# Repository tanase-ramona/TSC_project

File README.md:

## EBookReader

Am început realizarea proiectului pornind de la schema electrică oferită în enunț. Am adăugat fiecare componentă din biblioteca sugerata și le-am conectat corespunzător, atribuindu-le etichete adecvate. După finalizarea conexiunilor, am rulat o verificare ERC pentru a identifica eventualele erori si am rezolvat marea majoritate. A rămas o singură eroare nerezolvată, deoarece Fusion nu a putut indica locația acesteia. După ce schema a fost finalizată, am trecut la partea de PCB. Am decupat placa conform dimensiunilor cerute folosind masuratorile oferite de Fusion. Cea mai mare provocare a fost identificarea și poziționarea corectă a componentelor pe PGB. După plasare, am realizat rutarea și am validat designul în funcție de regulile specificate în enunț. Pentru a elimina erorile, a fost necesară modificarea footprint-ului pentru anumite piese. În final, am realizat planul de masă atât pentru stratul superior, cât și pentru cel inferior.

## Arhitectură Generală a Sistemului

## Descriere Generală

Modulul **ESP32-C6-WROOM-1-N8** este nucleul sistemului, facilitând comunicarea cu toate celelalte periferice prin interfețe standard precum I2C, SPI și GPIO. Alimentarea este realizată printr-o baterie Li-Po, gestionată de un controler de încărcare dedicat și monitorizată constant cu ajutorul unui fuel gauge.

## Componente Hardware

###  ESP32-C6
- Microcontroller cu procesor RISC-V
- Conectivitate Wi-Fi 6 și Bluetooth LE
- Interfețe: SPI, I2C, UART, GPIO
- Tensiune de operare: 3.3V

### Componente și resurse

| Componentă  | Link Achiziție | Datasheet |
|-------------|----------------|-----------|
| BOOT_BUTTON | https://ro.mouser.com/ProductDetail/Panasonic/EVQ-P7L01P | https://componentsearchengine.com/Datasheets/2/EVQP7L01P.pdf |
| C1          | https://ro.mouser.com/ProductDetail/YAGEO/CC0402MRX5R5BB106 | https://componentsearchengine.com/Datasheets/2/CC0402MRX5R5BB106.pdf |
| C1_BAT      | https://ro.mouser.com/ProductDetail/YAGEO/CC0402MRX5R5BB106 | https://componentsearchengine.com/Datasheets/2/CC0402MRX5R5BB106.pdf |
| C2          | https://ro.mouser.com/ProductDetail/YAGEO/CC0402MRX5R5BB106 | https://componentsearchengine.com/Datasheets/2/CC0402MRX5R5BB106.pdf |
| C2_BAT      | https://ro.mouser.com/ProductDetail/YAGEO/CC0402MRX5R5BB106 | https://componentsearchengine.com/Datasheets/2/CC0402MRX5R5BB106.pdf |
| C3          | https://ro.mouser.com/ProductDetail/YAGEO/CC0402MRX5R5BB106 | https://componentsearchengine.com/Datasheets/2/CC0402MRX5R5BB106.pdf |
| C4          | https://ro.mouser.com/ProductDetail/YAGEO/CC0402MRX5R5BB106 | https://componentsearchengine.com/Datasheets/2/CC0402MRX5R5BB106.pdf |
| C4_USB      | https://ro.mouser.com/ProductDetail/YAGEO/CC0402MRX5R5BB106 | https://componentsearchengine.com/Datasheets/2/CC0402MRX5R5BB106.pdf |
| C5          | https://ro.mouser.com/ProductDetail/YAGEO/CC0402MRX5R5BB106 | https://componentsearchengine.com/Datasheets/2/CC0402MRX5R5BB106.pdf |
| C5_USB      | https://ro.mouser.com/ProductDetail/YAGEO/CC0402MRX5R5BB106 | https://componentsearchengine.com/Datasheets/2/CC0402MRX5R5BB106.pdf |
| C6          | https://ro.mouser.com/ProductDetail/YAGEO/CC0402MRX5R5BB106 | https://componentsearchengine.com/Datasheets/2/CC0402MRX5R5BB106.pdf |
| C7          | https://ro.mouser.com/ProductDetail/YAGEO/CC0402MRX5R5BB106 | https://componentsearchengine.com/Datasheets/2/CC0402MRX5R5BB106.pdf |
| C8          | https://ro.mouser.com/ProductDetail/YAGEO/CC0402MRX5R5BB106 | https://componentsearchengine.com/Datasheets/2/CC0402MRX5R5BB106.pdf |
| C9          | https://ro.mouser.com/ProductDetail/YAGEO/CC0402MRX5R5BB106 | https://componentsearchengine.com/Datasheets/2/CC0402MRX5R5BB106.pdf |
| C10         | https://ro.mouser.com/ProductDetail/YAGEO/CC0402MRX5R5BB106 | https://componentsearchengine.com/Datasheets/2/CC0402MRX5R5BB106.pdf |
| D1          | https://ro.mouser.com/ProductDetail/STMicroelectronics/STPS2L30A | https://www.st.com/resource/en/datasheet/stps2l30.pdf |
| D2          | https://ro.mouser.com/ProductDetail/STMicroelectronics/STPS2L30A | https://www.st.com/resource/en/datasheet/stps2l30.pdf |
| D3          | https://ro.mouser.com/ProductDetail/STMicroelectronics/STPS2L30A | https://www.st.com/resource/en/datasheet/stps2l30.pdf |
| D4          | https://ro.mouser.com/ProductDetail/STMicroelectronics/STPS2L30A | https://www.st.com/resource/en/datasheet/stps2l30.pdf |
| IC1         | https://ro.mouser.com/ProductDetail/Texas-Instruments/BQ24075RGTT | https://www.ti.com/lit/ds/symlink/bq24075.pdf |
| Q1          | https://ro.mouser.com/ProductDetail/Diodes-Incorporated/DMG2305UX-7 | https://www.diodes.com/assets/Datasheets/ds31771.pdf |
| Q2          | https://ro.mouser.com/ProductDetail/Diodes-Incorporated/DMG2305UX-7 | https://www.diodes.com/assets/Datasheets/ds31771.pdf |
| Q3          | https://ro.mouser.com/ProductDetail/Diodes-Incorporated/DMG2305UX-7 | https://www.diodes.com/assets/Datasheets/ds31771.pdf |
| Q4          | https://ro.mouser.com/ProductDetail/Diodes-Incorporated/DMG2305UX-7 | https://www.diodes.com/assets/Datasheets/ds31771.pdf |
| R1          | https://ro.mouser.com/ProductDetail/YAGEO/RC0402FR-0710KL | https://componentsearchengine.com/Datasheets/2/RC0402FR-0710KL.pdf |
| R2          | https://ro.mouser.com/ProductDetail/YAGEO/RC0402FR-0710KL | https://componentsearchengine.com/Datasheets/2/RC0402FR-0710KL.pdf |
| R3          | https://ro.mouser.com/ProductDetail/YAGEO/RC0402FR-0710KL | https://componentsearchengine.com/Datasheets/2/RC0402FR-0710KL.pdf |
| R4          | https://ro.mouser.com/ProductDetail/YAGEO/RC0402FR-0710KL | https://componentsearchengine.com/Datasheets/2/RC0402FR-0710KL.pdf |
| R5           | https://ro.mouser.com/ProductDetail/YAGEO/RC0402FR-07100KL | https://ro.mouser.com/datasheet/2/447/YAGEO_PYu_RC_Group_51_RoHS_L_12-3313492.pdf |
| R6           | https://ro.mouser.com/ProductDetail/YAGEO/RC0402FR-07100KL | https://ro.mouser.com/datasheet/2/447/YAGEO_PYu_RC_Group_51_RoHS_L_12-3313492.pdf |
| R7           | https://ro.mouser.com/ProductDetail/YAGEO/RC0402FR-07100KL | https://ro.mouser.com/datasheet/2/447/YAGEO_PYu_RC_Group_51_RoHS_L_12-3313492.pdf |
| R8           | https://ro.mouser.com/ProductDetail/YAGEO/RC0402FR-07100KL | https://ro.mouser.com/datasheet/2/447/YAGEO_PYu_RC_Group_51_RoHS_L_12-3313492.pdf |
| R9           | https://ro.mouser.com/ProductDetail/YAGEO/RC0402FR-07100KL | https://ro.mouser.com/datasheet/2/447/YAGEO_PYu_RC_Group_51_RoHS_L_12-3313492.pdf |
| R10          | https://ro.mouser.com/ProductDetail/YAGEO/RC0402FR-07100KL | https://ro.mouser.com/datasheet/2/447/YAGEO_PYu_RC_Group_51_RoHS_L_12-3313492.pdf |
| RESET_BUTTON | https://ro.mouser.com/ProductDetail/Panasonic/EVQ-P7L01P | https://componentsearchengine.com/Datasheets/2/EVQP7L01P.pdf |
| R_BOOT       | https://ro.mouser.com/ProductDetail/YAGEO/RC0402FR-07100KL | https://ro.mouser.com/datasheet/2/447/YAGEO_PYu_RC_Group_51_RoHS_L_12-3313492.pdf |
| R_CAPACITOR  | https://ro.mouser.com/ProductDetail/YAGEO/RC0402FR-07100KL | https://ro.mouser.com/datasheet/2/447/YAGEO_PYu_RC_Group_51_RoHS_L_12-3313492.pdf |
| R_CHANGE     | https://ro.mouser.com/ProductDetail/YAGEO/RC0402FR-07100KL | https://ro.mouser.com/datasheet/2/447/YAGEO_PYu_RC_Group_51_RoHS_L_12-3313492.pdf |
| R_CL1        | https://ro.mouser.com/ProductDetail/YAGEO/RC0402FR-07100KL | https://ro.mouser.com/datasheet/2/447/YAGEO_PYu_RC_Group_51_RoHS_L_12-3313492.pdf |
| R_RESET      | https://ro.mouser.com/ProductDetail/YAGEO/RC0402FR-07100KL | https://ro.mouser.com/datasheet/2/447/YAGEO_PYu_RC_Group_51_RoHS_L_12-3313492.pdf |
| SENSOR2      | https://ro.mouser.com/ProductDetail/Bosch-Sensortec/BME680 | https://ro.mouser.com/datasheet/2/783/BST_BME680_DS001-1509608.pdf |
| SJ1          | https://grabcad.com/library/solder-jumpers-1 | https://grabcad.com/library/solder-jumpers-1 |
| U1           | https://ro.mouser.com/ProductDetail/Winbond/W25Q512JVEIQ | https://ro.mouser.com/datasheet/2/949/Winbond_W25Q512JV_Datasheet-3240039.pdf |
| U2           | https://ro.mouser.com/ProductDetail/Espressif-Systems/ESP32-C6-WROOM-1-N8 | https://ro.mouser.com/datasheet/2/891/Espressif_ESP32_C6_WROOM_1__Datasheet_V0_1_PRELIMI-3239987.pdf |
| U3           | https://ro.mouser.com/ProductDetail/Analog-Devices-Maxim-Integrated/DS3231SN | https://ro.mouser.com/datasheet/2/609/DS3231-3421123.pdf |
| U4           | https://ro.mouser.com/ProductDetail/Analog-Devices-Maxim-Integrated/MAX17048G+T10 | https://ro.mouser.com/datasheet/2/609/MAX17048_MAX17049-3469099.pdf |
| U5           | https://ro.mouser.com/ProductDetail/Microchip-Technology/MCP73831T-2ACI-OT | https://ro.mouser.com/datasheet/2/268/MCP73831_Family_Data_Sheet_DS20001984H-3441711.pdf |

###  Sistem de Alimentare
- **MCP73831** – controler de încărcare pentru baterii LiPo
- **MAX17048** – fuel gauge pentru măsurarea nivelului de baterie și avertizare
- **XC6220A331MR** – stabilizator de tensiune 3.3V LDO

###  Protecție și Conectivitate
- Protecție ESD pentru liniile USB (USBLC6)
- Diode Schottky pentru protecție la supratensiune
- Conector USB-C pentru alimentare și comunicație serială

###  Interfață Utilizator
- Buton RESET pentru restart manual
- LED pentru indicarea stării de încărcare

## Estimare Totală Consum în Funcționare Activă:
**~120 – 200 mA** (fără SD Card)

## Estimare Totală în Modul Sleep:
**< 100 µA** (cu ESP32 în deep sleep și periferice oprite)

---

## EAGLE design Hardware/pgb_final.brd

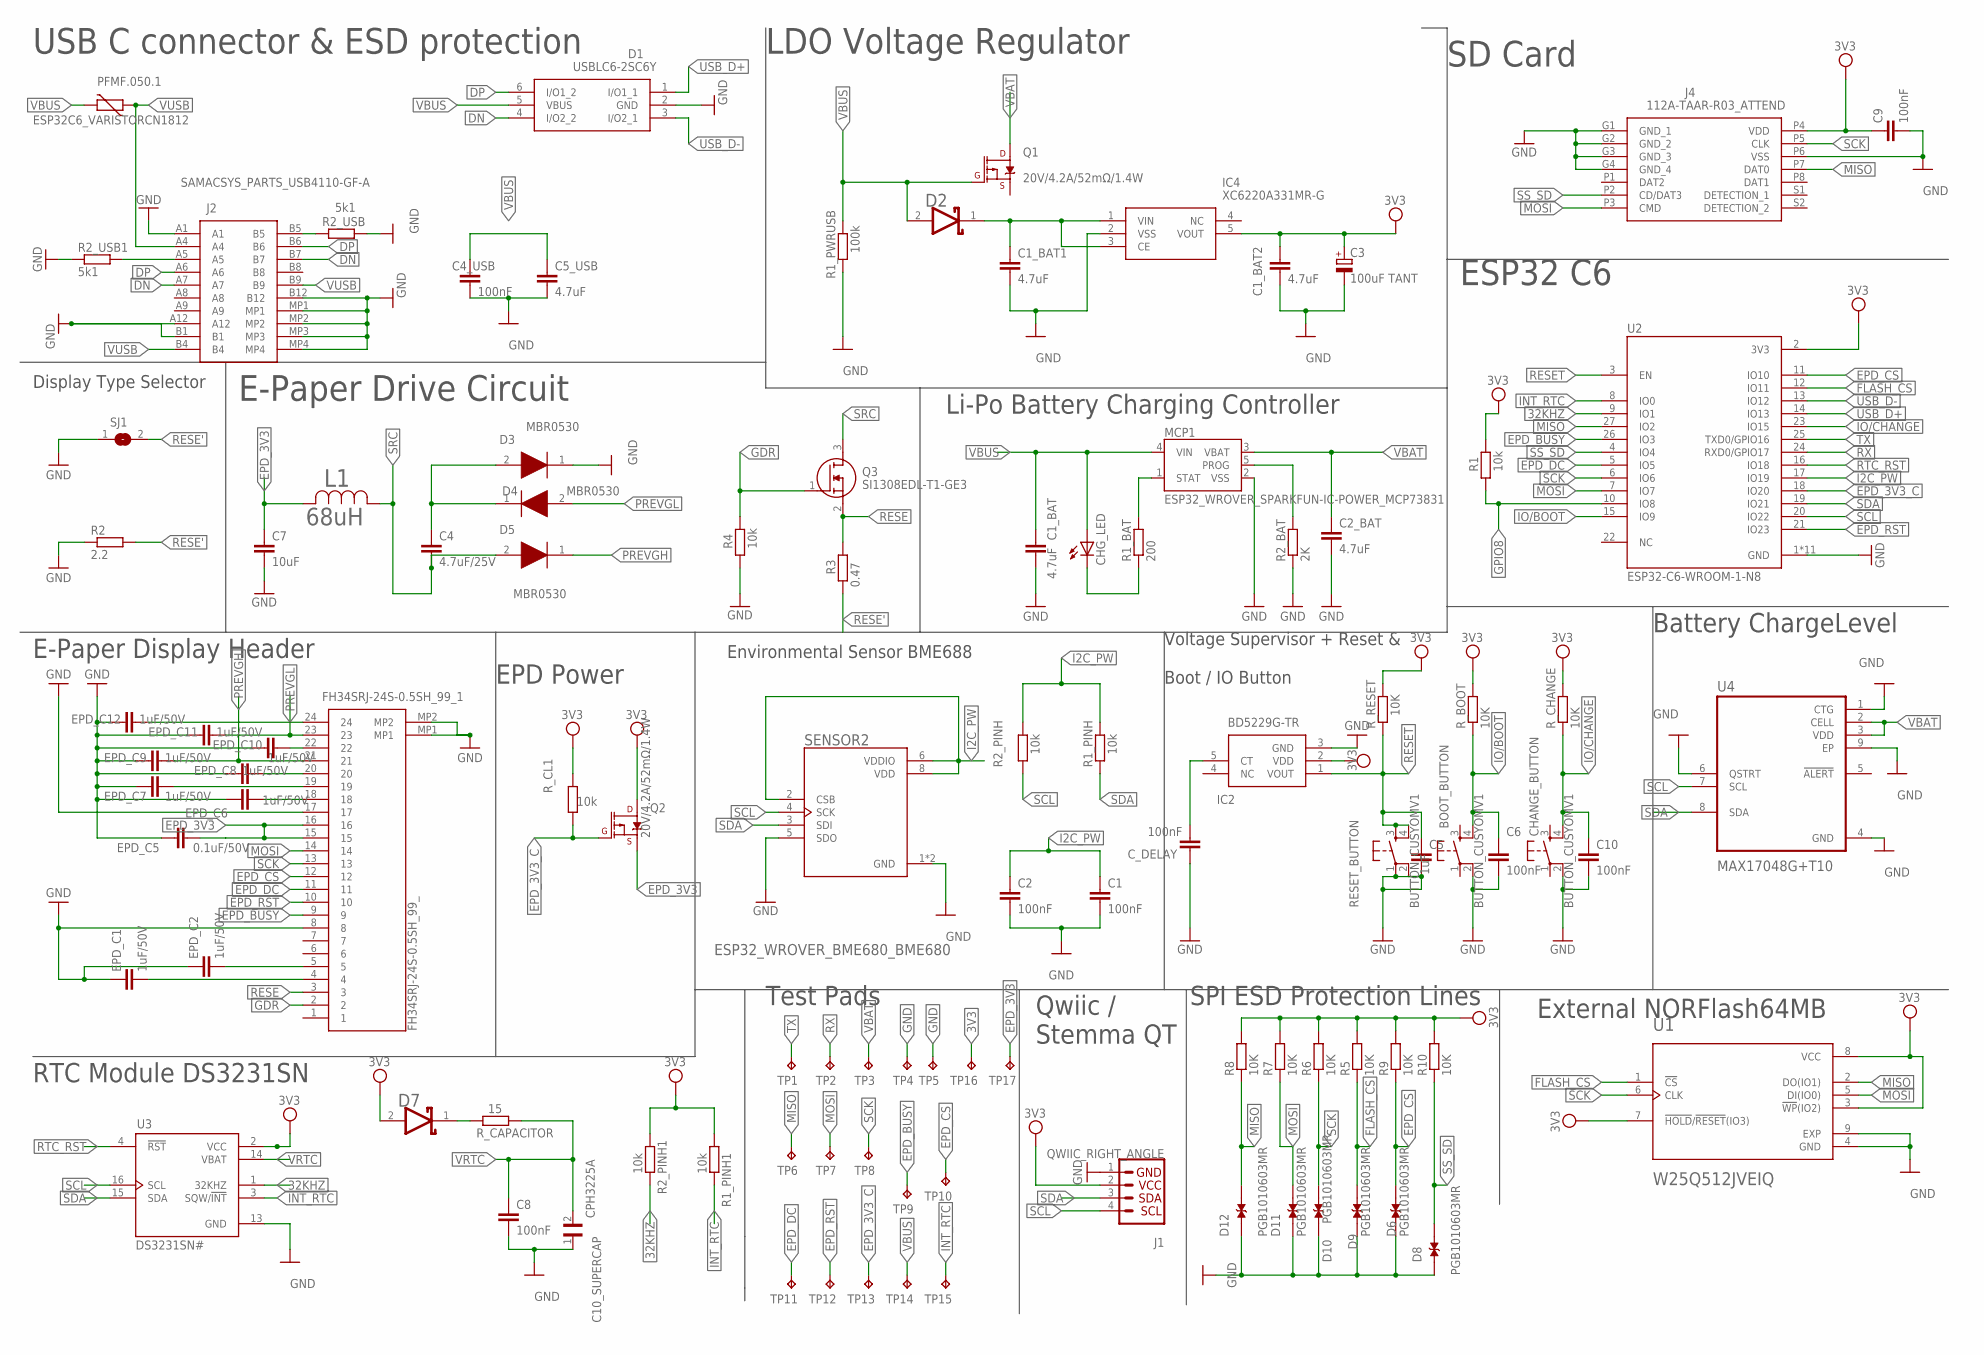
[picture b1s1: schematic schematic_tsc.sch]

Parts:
BOOT_BUTTON: BUTTON_CUSYOMV1; MYBUTTON
C1, C2, C4_USB, C6, C8, C9, C10: 100nF; EAGLE-LTSPICE_C0402
C1_BAT, C1_BAT1, C1_BAT2, C2_BAT, C5_USB: 4.7uF; EAGLE-LTSPICE_C0402
C3: 100uF TANT; RCL_CT3528
C4: 4.7uF/25V; EAGLE-LTSPICE_C0402
C5: 1uF; EAGLE-LTSPICE_C0402
C7: 10uF; EAGLE-LTSPICE_C0402
C10_SUPERCAP: CPH3225A; CAPCP3225X100N
CHANGE_BUTTON: BUTTON_CUSYOMV1; MYBUTTON
CHG_LED: ADAFRUIT_LEDCHIP-LED0603; ADAFRUIT_CHIP-LED0603
C_DELAY: 100nF; EAGLE-LTSPICE_C0402
D1: USBLC6-2SC6Y; SOT95P280X145-6N
D2, D7: ESP32_WROVER_AVX---SD0805S020S1R0_AVX_SD0805S020S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; ESP32_WROVER_AVX---SD0805S020S1R0_AVX_SD0805S020S1R0_0
D3, D4, D5: MBR0530; SOD3716X135N
D6, D8, D9, D10, D11, D12: PGB1010603MR; DIOC1608X36N
EPD_C1, EPD_C2, EPD_C6, EPD_C7, EPD_C8, EPD_C9, EPD_C10, EPD_C11, EPD_C12: 1uF/50V; EAGLE-LTSPICE_C0402
EPD_C5: 0.1uF/50V; EAGLE-LTSPICE_C0402
FH34SRJ-24S-0.5SH_99_1: FH34SRJ-24S-0.5SH_99_; FH34SRJ24S05SH99
IC2: BD5229G-TR; SOT95P280X125-5N
IC4: XC6220A331MR-G; SOT95P280X120-5N
J1: QWIIC_RIGHT_ANGLE; JST04_1MM_RA
J2: SAMACSYS_PARTS_USB4110-GF-A; SAMACSYS_PARTS_USB4110GFA
J4: 112A-TAAR-R03_ATTEND; 112ATAARR03ATTEND
L1: 68uH; IND_4828-WE-TPC_WRE
MCP1: ESP32_WROVER_SPARKFUN-IC-POWER_MCP73831; ESP32_WROVER_SPARKFUN-IC-POWER_SOT23-5
PFMF.050.1: ESP32C6_VARISTORCN1812; ESP32C6_VARISTOR_CT/CN1812
Q1, Q2: 20V/4.2A/52mΩ/1.4W; ESP32_WROVER_SPARKFUN-DISCRETESEMI_SOT23-3
Q3: SI1308EDL-T1-GE3; SOT65P210X110-3N
R1, R1_PINH, R1_PINH1, R2_PINH, R2_PINH1, R4: 10k; ESP32_WROVER_EAGLE-LTSPICE_R0402
R1_BAT: 200; ESP32_WROVER_EAGLE-LTSPICE_R0402
R1_PWRUSB: 100k; ESP32_WROVER_EAGLE-LTSPICE_R0402
R2: 2.2; ESP32_WROVER_EAGLE-LTSPICE_R0402
R2_BAT: 2K; ESP32_WROVER_EAGLE-LTSPICE_R0402
R2_USB, R2_USB1: 5k1; ESP32_WROVER_EAGLE-LTSPICE_R0402
R3: 0.47; ESP32_WROVER_EAGLE-LTSPICE_R0402
R5, R6, R7, R8, R9, R10: 10K; ESP32_WROVER_EAGLE-LTSPICE_R0402
RESET_BUTTON: BUTTON_CUSYOMV1; MYBUTTON
R_BOOT: 10K; ESP32_WROVER_EAGLE-LTSPICE_R0402
R_CAPACITOR: 15; ESP32_WROVER_EAGLE-LTSPICE_R0402
R_CHANGE: 10K; ESP32_WROVER_EAGLE-LTSPICE_R0402
R_CL1: 10k; ESP32_WROVER_EAGLE-LTSPICE_R0402
R_RESET: 10K; ESP32_WROVER_EAGLE-LTSPICE_R0402
SENSOR2: ESP32_WROVER_BME680_BME680; ESP32_WROVER_BME680_PSON80P300X300X100-8N
SJ1: SJ
TP1, TP2, TP3, TP4, TP5, TP6, TP7, TP8, TP9, TP10, TP11, TP12, TP13, TP14, TP15, TP16, TP17: TPTP20R; TP20R
U1: W25Q512JVEIQ; SON127P600X800X80-9N
U2: ESP32-C6-WROOM-1-N8; XCVR_ESP32-C6-WROOM-1-N8
U3: DS3231SN#; SOIC127P1032X265-16N
U4: MAX17048G+T10; SON50P200X200X80-9N

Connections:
3V3: C1_BAT2.1, C3.+, C9.1, D7.2 (ANODE), IC2.2 (VDD), IC4.5 (VOUT), J1.2, J4.P4 (VDD), Q2.3 (D), R1.2, R1_PINH1.1, R2_PINH1.1, R5.2, R6.2, R7.2, R8.2, R9.2, R10.2, R_BOOT.2, R_CHANGE.2, R_CL1.2, R_RESET.2, TP16.TP, U1.3 (!WP!(IO2)), U1.7 (!HOLD!/!RESET!(IO3)), U1.8 (VCC), U2.2 (3V3), U3.2 (VCC)
32KHZ: R2_PINH1.2, U2.9 (IO1), U3.1 (32KHZ)
DN: D1.4 (I/O2_2), J2.A7, J2.B7
DP: D1.6 (I/O1_2), J2.A6, J2.B6
EPD_3V3: C7.1, EPD_C5.2, FH34SRJ-24S-0.5SH_99_1.15, FH34SRJ-24S-0.5SH_99_1.16, L1.2, Q2.2 (S), TP17.TP
EPD_3V3_C: Q2.1 (G), R_CL1.1, TP13.TP, U2.18 (IO20)
EPD_BUSY: FH34SRJ-24S-0.5SH_99_1.9, TP9.TP, U2.26 (IO3)
EPD_CS: D6.2, FH34SRJ-24S-0.5SH_99_1.12, R9.1, TP10.TP, U2.11 (IO10)
EPD_DC: FH34SRJ-24S-0.5SH_99_1.11, TP11.TP, U2.5 (IO5)
EPD_RST: FH34SRJ-24S-0.5SH_99_1.10, TP12.TP, U2.21 (IO23)
FLASH_CS: D9.2, R5.1, U1.1 (!CS), U2.12 (IO11)
GDR: FH34SRJ-24S-0.5SH_99_1.2, Q3.1 (G), R4.2
GND: BOOT_BUTTON.2, C1.2, C1_BAT.2, C1_BAT1.2, C1_BAT2.2, C2.2, C2_BAT.2, C3.-, C4_USB.2, C5.2, C5_USB.2, C6.2, C7.2, C8.2, C9.2, C10.2, C10_SUPERCAP.1, CHANGE_BUTTON.2, C_DELAY.1, D1.2 (GND), D3.1 (K), D6.1, D8.1, D9.1, D10.1, D11.1, D12.1, EPD_C1.1, EPD_C2.1, EPD_C5.1, EPD_C6.1, EPD_C7.1, EPD_C8.1, EPD_C9.1, EPD_C10.1, EPD_C11.1, EPD_C12.1, FH34SRJ-24S-0.5SH_99_1.8, FH34SRJ-24S-0.5SH_99_1.17, FH34SRJ-24S-0.5SH_99_1.MP1, FH34SRJ-24S-0.5SH_99_1.MP2, IC2.3 (GND), IC4.2 (VSS), J1.1, J2.A1, J2.A12, J2.B1, J2.B12, J2.MP1, J2.MP2, J2.MP3, J2.MP4, J4.G1 (GND_1), J4.G2 (GND_2), J4.G3 (GND_3), J4.G4 (GND_4), J4.P6 (VSS), MCP1.2 (VSS), R1_PWRUSB.1, R2.1, R2_BAT.1, R2_USB.2, R2_USB1.1, R4.1, RESET_BUTTON.1, RESET_BUTTON.2, SENSOR2.1 (GND), SENSOR2.5 (SDO), SENSOR2.7 (GND), SJ1.1, TP4.TP, TP5.TP, U1.4 (GND), U1.9 (EXP), U2.1 (GND), U2.28 (GND), U2.29_1 (GND), U2.29_2 (GND), U2.29_3 (GND), U2.29_4 (GND), U2.29_5 (GND), U2.29_6 (GND), U2.29_7 (GND), U2.29_8 (GND), U2.29_9 (GND), U3.13 (GND), U4.1 (CTG), U4.4 (GND), U4.6 (QSTRT), U4.9 (EP)
GPIO8: R1.1, U2.10 (IO8)
I2C_PW: C1.1, C2.1, R1_PINH.2, R2_PINH.2, SENSOR2.2 (CSB), SENSOR2.6 (VDDIO), SENSOR2.8 (VDD), U2.17 (IO19)
INT_RTC: R1_PINH1.2, TP15.TP, U2.8 (IO0), U3.3 (SQW/!INT)
IO/BOOT: BOOT_BUTTON.4, C6.1, R_BOOT.1, U2.15 (IO9)
IO/CHANGE: C10.1, CHANGE_BUTTON.4, R_CHANGE.1, U2.23 (IO15)
MISO: D12.2, J4.P7 (DAT0), R8.1, TP6.TP, U1.2 (DO(IO1)), U2.27 (IO2)
MOSI: D11.2, FH34SRJ-24S-0.5SH_99_1.14, J4.P3 (CMD), R7.1, TP7.TP, U1.5 (DI(IO0)), U2.7 (IO7)
unnamed: EPD_C10.2, FH34SRJ-24S-0.5SH_99_1.22
unnamed: J2.A5, R2_USB1.2
unnamed: J2.B5, R2_USB.1
unnamed: C1_BAT1.1, D2.1 (CATHODE), IC4.1 (VIN), IC4.3 (CE)
unnamed: C4.1, D3.2 (A), D4.1 (K)
unnamed: MCP1.1 (STAT), R1_BAT.2
unnamed: CHG_LED.C, R1_BAT.1
unnamed: MCP1.5 (PROG), R2_BAT.2
unnamed: EPD_C12.2, FH34SRJ-24S-0.5SH_99_1.24
unnamed: EPD_C8.2, FH34SRJ-24S-0.5SH_99_1.20
unnamed: EPD_C7.2, FH34SRJ-24S-0.5SH_99_1.19
unnamed: EPD_C6.2, FH34SRJ-24S-0.5SH_99_1.18
unnamed: EPD_C2.2, FH34SRJ-24S-0.5SH_99_1.5
unnamed: EPD_C1.2, FH34SRJ-24S-0.5SH_99_1.4
unnamed: C_DELAY.2, IC2.5 (CT)
unnamed: D7.1 (CATHODE), R_CAPACITOR.2
PREVGH: D5.1 (K), EPD_C9.2, FH34SRJ-24S-0.5SH_99_1.21
PREVGL: D4.2 (A), EPD_C11.2, FH34SRJ-24S-0.5SH_99_1.23
RESE: FH34SRJ-24S-0.5SH_99_1.3, Q3.2 (S), R3.2
RESE': R2.2, R3.1, SJ1.2
RESET: C5.1, IC2.1 (VOUT), RESET_BUTTON.3, RESET_BUTTON.4, R_RESET.1, U2.3 (EN)
RTC_RST: U2.16 (IO18), U3.4 (!RST)
RX: TP2.TP, U2.24 (RXD0/GPIO17)
SCK: D10.2, FH34SRJ-24S-0.5SH_99_1.13, J4.P5 (CLK), R6.1, TP8.TP, U1.6 (CLK), U2.6 (IO6)
SCL: J1.4, R2_PINH.1, SENSOR2.4 (SCK), U2.20 (IO22), U3.16 (SCL), U4.7 (SCL)
SDA: J1.3, R1_PINH.1, SENSOR2.3 (SDI), U2.19 (IO21), U3.15 (SDA), U4.8 (SDA)
SRC: C4.2, D5.2 (A), L1.1, Q3.3 (D)
SS_SD: D8.2, J4.P2 (CD/DAT3), R10.1, U2.4 (IO4)
TX: TP1.TP, U2.25 (TXD0/GPIO16)
USB_D+: D1.1 (I/O1_1), U2.14 (IO13)
USB_D-: D1.3 (I/O2_1), U2.13 (IO12)
VBAT: C2_BAT.1, MCP1.3 (VBAT), Q1.3 (D), TP3.TP, U4.2 (CELL), U4.3 (VDD)
VBUS: C1_BAT.1, C4_USB.1, C5_USB.1, CHG_LED.A, D1.5 (VBUS), D2.2 (ANODE), MCP1.4 (VIN), PFMF.050.1.2, Q1.1 (G), R1_PWRUSB.2, TP14.TP
VRTC: C8.1, C10_SUPERCAP.2, R_CAPACITOR.1, U3.14 (VBAT)
VUSB: J2.A4, J2.B4, J2.B9, PFMF.050.1.1

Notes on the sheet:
SD Card
LDO Voltage Regulator
USB C connector & ESD protection
Display Type Selector
E-Paper Drive Circuit
Li-Po Battery Charging Controller
ESP32 C6
E-Paper Display Header
EPD Power
Environmental Sensor BME688
Voltage Supervisor + Reset & Boot / IO Button
Battery ChargeLevel
RTC Module DS3231SN
Test Pads
Qwiic / Stemma QT
SPI ESD Protection Lines
External NORFlash64MB

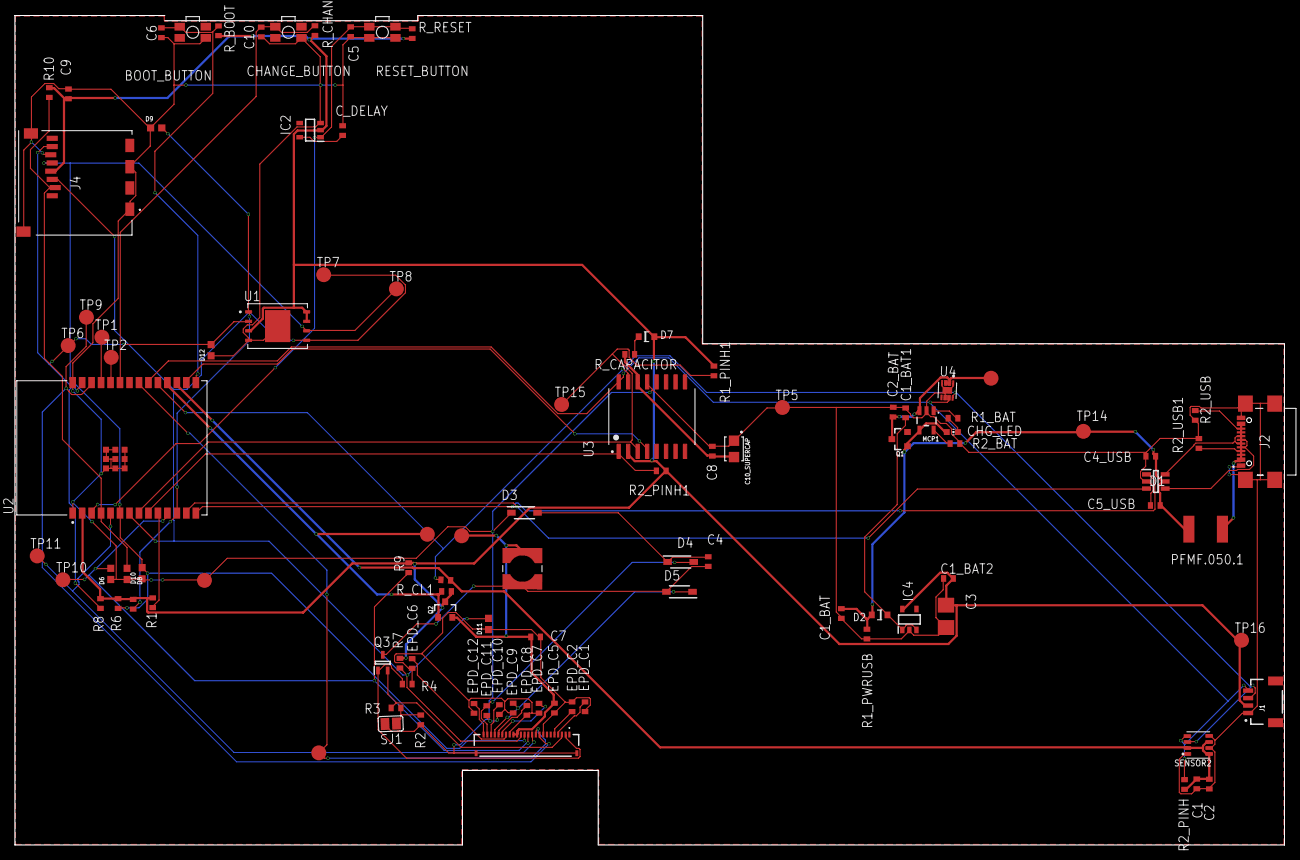
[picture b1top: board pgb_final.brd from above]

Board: 2 copper layers, 170.2 x 111.2 mm, 103 parts (0 on the bottom side), 55 nets.

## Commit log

2025-04-14 Create LICENSE
2025-04-15 Create Mechanical

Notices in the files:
parts and their libraries:
COPYRIGHT: Copyright (C) 2024 Ultra Librarian. All rights reserved.
